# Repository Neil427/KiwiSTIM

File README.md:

# KiwiSTIM
KiwiSTIM is a engine simulator used for testing engine management computers, it is variation of Ardustim and uses the Ardustim firmware. 
It has 2 Nanos for 2 switchable trigger setups, 2x crank/cam leds, 8x analog pots, 8x injector leds, 8x ignition leds, 8x digital output leds, stepper iac leds, 4x digital input switches.

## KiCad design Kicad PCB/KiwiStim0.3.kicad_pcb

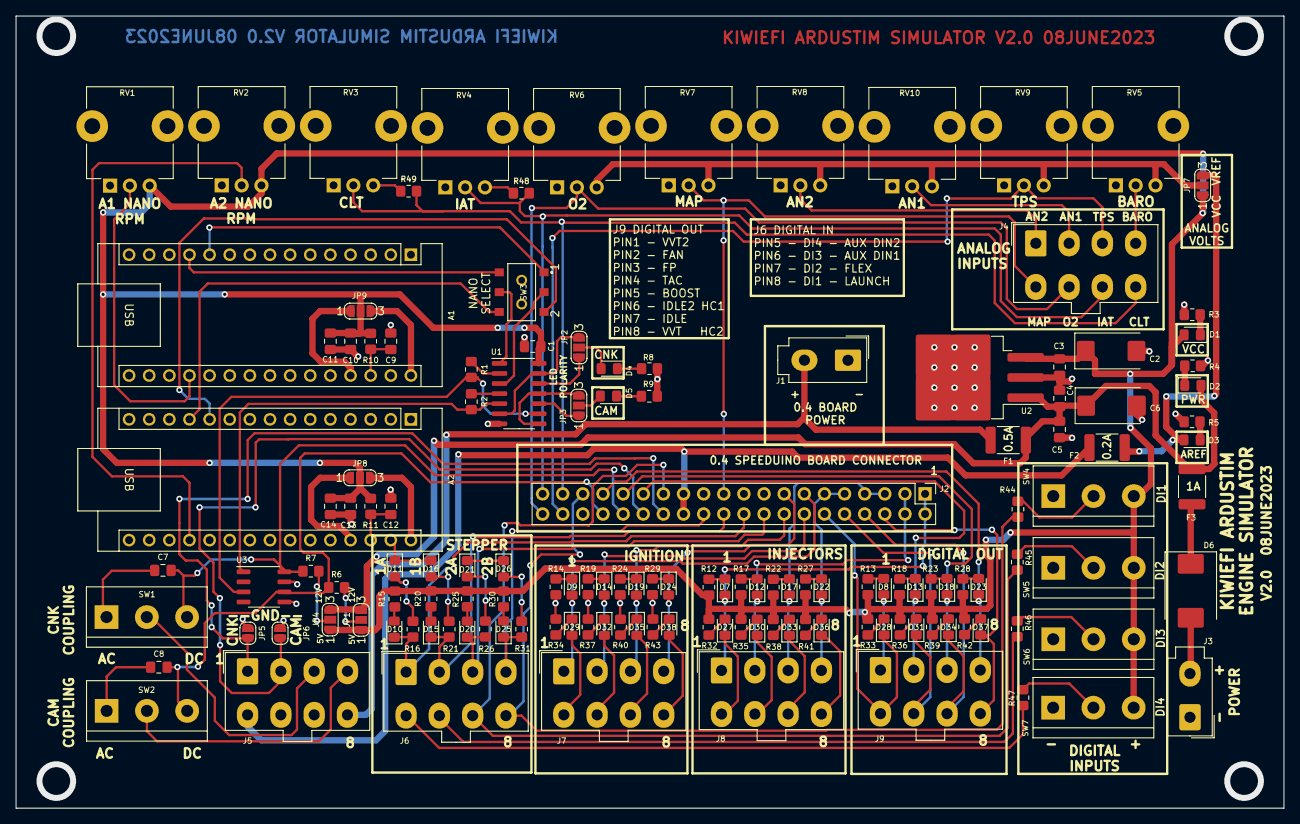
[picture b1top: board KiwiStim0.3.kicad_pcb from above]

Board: 2 copper layers, 160.0 x 99.9 mm, 144 parts (0 on the bottom side), 124 nets.

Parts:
A1, A2: ArduinoNANO; Arduino_Nano
C1, C3, C4, C10, C13: 100N; C_0805_2012Metric_Pad1.18x1.45mm_HandSolder
C2, C6: 22uF 25V; CP_EIA-7343-31_Kemet-D_Pad2.25x2.55mm_HandSolder
C5, C7, C8, C9, C11, C12, C14: 1uF; C_0805_2012Metric_Pad1.18x1.45mm_HandSolder
D1: VCC LED; LED_0805_2012Metric_Pad1.15x1.40mm_HandSolder
D2: PWR LED; LED_0805_2012Metric_Pad1.15x1.40mm_HandSolder
D3: AREF LED; LED_0805_2012Metric_Pad1.15x1.40mm_HandSolder
D4: CNK LED; LED_0805_2012Metric_Pad1.15x1.40mm_HandSolder
D5: CAM LED; LED_0805_2012Metric_Pad1.15x1.40mm_HandSolder
D6: B360; D_SMC
D7, D8, D9, D10, D11, D12, D13, D14, D15, D16, D17, D18, D19, D20, D21, D22, D23, D24, D25, D26, D27, D28, D29, D30, D31, D32, D33, D34, D35, D36, D37, D38: LED; LED_0805_2012Metric_Pad1.15x1.40mm_HandSolder
F1: 0.5A ECU POWER; Fuse_1812_4532Metric_Pad1.30x3.40mm_HandSolder
F2: 0.2A ECU VREF; Fuse_1812_4532Metric_Pad1.30x3.40mm_HandSolder
F3: 1A POWER; Fuse_1812_4532Metric_Pad1.30x3.40mm_HandSolder
J1: 0.4 POWER; Molex_Mini-Fit_Jr_5566-02A_2x01_P4.20mm_Vertical
J2: 0.4 BOARD CONNECTOR; PinHeader_2x20_P2.54mm_Vertical
J3: POWER; Molex_Mini-Fit_Jr_5566-02A_2x01_P4.20mm_Vertical
J4: ANALOG INPUTS; Molex_Mini-Fit_Jr_5566-08A_2x04_P4.20mm_Vertical
J5: BASIC; Molex_Mini-Fit_Jr_5566-08A_2x04_P4.20mm_Vertical
J6: MISC.; Molex_Mini-Fit_Jr_5566-08A_2x04_P4.20mm_Vertical
J7: IGNITION; Molex_Mini-Fit_Jr_5566-08A_2x04_P4.20mm_Vertical
J8: INJECTORS; Molex_Mini-Fit_Jr_5566-08A_2x04_P4.20mm_Vertical
J9: DIGITAL; Molex_Mini-Fit_Jr_5566-08A_2x04_P4.20mm_Vertical
JP1: CAM PULLUP; SolderJumper-3_P1.3mm_Open_RoundedPad1.0x1.5mm_NumberLabels
JP2: CNK LED POLARITY; SolderJumper-3_P1.3mm_Open_RoundedPad1.0x1.5mm_NumberLabels
JP3: CAM LED POLARITY; SolderJumper-3_P1.3mm_Open_RoundedPad1.0x1.5mm_NumberLabels
JP4: CRANK PULLUP; SolderJumper-3_P1.3mm_Open_RoundedPad1.0x1.5mm_NumberLabels
JP5: CNK GND; SolderJumper-2_P1.3mm_Open_RoundedPad1.0x1.5mm
JP6: CAM GND; SolderJumper-2_P1.3mm_Open_RoundedPad1.0x1.5mm
JP7: ANALOG VREF; SolderJumper-3_P1.3mm_Open_RoundedPad1.0x1.5mm_NumberLabels
JP8: A2 PWR; SolderJumper-3_P1.3mm_Open_RoundedPad1.0x1.5mm_NumberLabels
JP9: A1 PWR; SolderJumper-3_P1.3mm_Open_RoundedPad1.0x1.5mm_NumberLabels
R1, R2, R6, R7, R10, R11: 470; R_0805_2012Metric_Pad1.20x1.40mm_HandSolder
R3, R4, R5, R12, R13, R14, R15, R16, R17, R18, R19, R20, R21, R22, R23, R24, R25, R26, R27, R28, R29, R30, R31, R32, R33, R34, R35, R36, R37, R38, R39, R40, R41, R42, R43: 1K; R_0805_2012Metric_Pad1.20x1.40mm_HandSolder
R8, R9: 470R; R_0805_2012Metric_Pad1.20x1.40mm_HandSolder
R44, R45, R46, R47: 220; R_0805_2012Metric_Pad1.20x1.40mm_HandSolder
R48, R49: 10K; R_0805_2012Metric_Pad1.20x1.40mm_HandSolder
RV1, RV2, RV3, RV4, RV5, RV6, RV7, RV8, RV9, RV10: 10K; Potentiometer_TT_P0915N
SW1: CKP COUPLING; TerminalBlock_bornier-3_P5.08mm
SW2: CMP COUPLING; TerminalBlock_bornier-3_P5.08mm
SW3: DPDT; AYZ0202AGRLC
SW4: DI1 SWITCH; TerminalBlock_bornier-3_P5.08mm
SW5: DI2 SWITCH; TerminalBlock_bornier-3_P5.08mm
SW6: DI3 SWITCH; TerminalBlock_bornier-3_P5.08mm
SW7: DI4 SWITCH; TerminalBlock_bornier-3_P5.08mm
U1: 74HC14; SOIC-14_3.9x8.7mm_P1.27mm
U2: LM2937-5; TO-263-3_TabPin2
U3: VNLD5090; SO-8_3.9x4.9mm_P1.27mm

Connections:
04PWR: F1.2, J1.2, J5.8
AN1: J4.2, RV10.2
AN2: J4.1, RV8.2
AVREF: D3.2 (A), F2.1, JP7.3 (B)
BARO: J4.4, RV5.2
CAM: SW3.5 (B), U1.1
CAM-: J2.30, J5.2, JP6.2 (B)
CKP: C7.2, J2.32, R7.1, SW1.3 (C), U3.8 (DRAIN1)
CLT: J2.37, J4.8, R49.1, RV3.2
CMP: C8.2, J2.34, R6.1, SW2.3 (C), U3.6 (DRAIN2)
CNK: SW3.2 (B), U1.3
CNK-: J2.28, J5.1, JP5.2 (B)
D1: D8.1 (K), J9.1
D2: D13.1 (K), J2.29, J9.2
D3: D18.1 (K), J2.31, J9.3
D4: D23.1 (K), J2.33, J9.4
D5: D28.1 (K), J2.12, J9.5
D6: D31.1 (K), J2.10, J9.6
D7: D34.1 (K), J2.8, J9.7
D8: D37.1 (K), J2.6, J9.8
DI1: J2.35, J6.8, R44.1
DI2: J2.27, J6.7, R45.1
DI3: J6.6, R46.1
DI4: J6.5, R47.1
GND: A1.4 (GND), A1.29 (GND), A2.4 (GND), A2.29 (GND), C1.2, C2.2, C3.2, C4.2, C5.2, C6.2, C9.2, C10.2, C11.2, C12.2, C13.2, C14.2, D11.1 (K), D16.1 (K), D21.1 (K), D26.1 (K), J1.1, J2.17, J2.19, J2.23, J2.36, J3.1, J5.6, J5.7, JP5.1 (A), JP6.1 (A), R3.2, R4.2, R5.2, R8.2, R9.2, R14.2, R19.2, R24.2, R29.2, R34.2, R37.2, R40.2, R43.2, R48.2, R49.2, RV1.1, RV2.1, RV3.3, RV4.3, RV5.1, RV6.1, RV7.1, RV8.1, RV9.1, RV10.1, SW4.1 (A), SW5.1 (A), SW6.1 (A), SW7.1 (A), U1.7 (GND), U2.2 (GND), U3.5 (SOURCE2), U3.7 (SOURCE1)
IAT: J2.39, J4.7, R48.1, RV4.2
IGN1: D9.2 (A), J2.13, J7.1
IGN2: D14.2 (A), J2.14, J7.2
IGN3: D19.2 (A), J2.16, J7.3
IGN4: D24.2 (A), J2.15, J7.4
IGN5: D29.2 (A), J7.5
IGN6: D32.2 (A), J7.6
IGN7: D35.2 (A), J7.7
IGN8: D38.2 (A), J7.8
INJ1: D7.1 (K), J2.1, J2.2, J8.1
INJ2: D12.1 (K), J2.3, J2.4, J8.2
INJ3: D17.1 (K), J2.5, J2.7, J8.3
INJ4: D22.1 (K), J2.9, J2.11, J8.4
INJ5: D27.1 (K), J8.5
INJ6: D30.1 (K), J8.6
INJ7: D33.1 (K), J8.7
INJ8: D36.1 (K), J8.8
MAP: J2.21, J4.5, RV7.2
unnamed: A1.27 (+5V), JP9.1 (A)
unnamed: A1.19 (A0), RV1.2
unnamed: A1.11 (D8), SW3.1 (A)
unnamed: A1.12 (D9), SW3.4 (A)
unnamed: A1.28 (RESET), C9.1, R10.2
unnamed: A1.30 (VIN), JP9.3 (B)
unnamed: A2.27 (+5V), JP8.1 (A)
unnamed: A2.19 (A0), RV2.2
unnamed: A2.11 (D8), SW3.3 (C)
unnamed: A2.12 (D9), SW3.6 (C)
unnamed: A2.28 (RESET), C12.1, R11.2
unnamed: A2.30 (VIN), JP8.3 (B)
unnamed: D1.1 (K), R3.1
unnamed: D2.1 (K), R4.1
unnamed: D3.1 (K), R5.1
unnamed: D4.2 (A), JP2.2 (C)
unnamed: D4.1 (K), R8.1
unnamed: D5.2 (A), JP3.2 (C)
unnamed: D5.1 (K), R9.1
unnamed: D6.2 (A), J3.2
unnamed: D6.1 (K), F3.2
unnamed: D7.2 (A), R12.1
unnamed: D8.2 (A), R13.1
unnamed: D9.1 (K), R14.1
unnamed: D10.2 (A), R15.1
unnamed: D11.2 (A), R16.1
unnamed: D12.2 (A), R17.1
unnamed: D13.2 (A), R18.1
unnamed: D14.1 (K), R19.1
unnamed: D15.2 (A), R20.1
unnamed: D16.2 (A), R21.1
unnamed: D17.2 (A), R22.1
unnamed: D18.2 (A), R23.1
unnamed: D19.1 (K), R24.1
unnamed: D20.2 (A), R25.1
unnamed: D21.2 (A), R26.1
unnamed: D22.2 (A), R27.1
unnamed: D23.2 (A), R28.1
unnamed: D24.1 (K), R29.1
unnamed: D25.2 (A), R30.1
unnamed: D26.2 (A), R31.1
unnamed: D27.2 (A), R32.1
unnamed: D28.2 (A), R33.1
unnamed: D29.1 (K), R34.1
unnamed: D30.2 (A), R35.1
unnamed: D31.2 (A), R36.1
unnamed: D32.1 (K), R37.1
unnamed: D33.2 (A), R38.1
unnamed: D34.2 (A), R39.1
unnamed: D35.1 (K), R40.1
unnamed: D36.2 (A), R41.1
unnamed: D37.2 (A), R42.1
unnamed: D38.1 (K), R43.1
unnamed: J5.3, SW1.2 (B)
unnamed: J5.4, SW2.2 (B)
unnamed: JP1.2 (C), R6.2
unnamed: JP2.1 (A), U1.12
unnamed: JP2.3 (B), U1.6, U1.13
unnamed: JP3.1 (A), U1.10
unnamed: JP3.3 (B), U1.8, U1.11
unnamed: JP4.2 (C), R7.2
unnamed: JP7.2 (C), RV5.3, RV6.3, RV7.3, RV8.3, RV9.3, RV10.3
unnamed: R1.1, U1.2
unnamed: R2.1, U1.4
unnamed: C7.1, SW1.1 (A)
unnamed: C8.1, SW2.1 (A)
unnamed: R44.2, SW4.2 (B)
unnamed: R45.2, SW5.2 (B)
unnamed: R46.2, SW6.2 (B)
unnamed: R47.2, SW7.2 (B)
unnamed: R2.2, U1.5, U3.1 (IN1)
unnamed: R1.2, U1.9, U3.3 (IN2)
O2: J2.40, J4.6, RV6.2
PWR: C4.1, C5.1, C6.1, D2.2 (A), F1.1, F3.1, JP1.3 (B), JP4.3 (B), U2.1 (VI)
STEP1A: D10.1 (K), J2.20, J6.1, R16.2
STEP1B: D15.1 (K), J2.22, J6.2, R21.2
STEP2A: D20.1 (K), J2.18, J6.3, R26.2
STEP2B: D25.1 (K), J2.24, J6.4, R31.2
TPS: J2.38, J4.3, RV9.2
VCC: C1.1, C2.1, C3.1, C10.1, C11.1, C13.1, C14.1, D1.2 (A), JP1.1 (A), JP4.1 (A), JP7.1 (A), JP8.2 (C), JP9.2 (C), R10.1, R11.1, R12.2, R13.2, R15.2, R17.2, R18.2, R20.2, R22.2, R23.2, R25.2, R27.2, R28.2, R30.2, R32.2, R33.2, R35.2, R36.2, R38.2, R39.2, R41.2, R42.2, RV1.3, RV2.3, SW4.3 (C), SW5.3 (C), SW6.3 (C), SW7.3 (C), U1.14 (VCC), U2.3 (VO)
VREF: F2.2, J2.25, J2.26, J5.5
